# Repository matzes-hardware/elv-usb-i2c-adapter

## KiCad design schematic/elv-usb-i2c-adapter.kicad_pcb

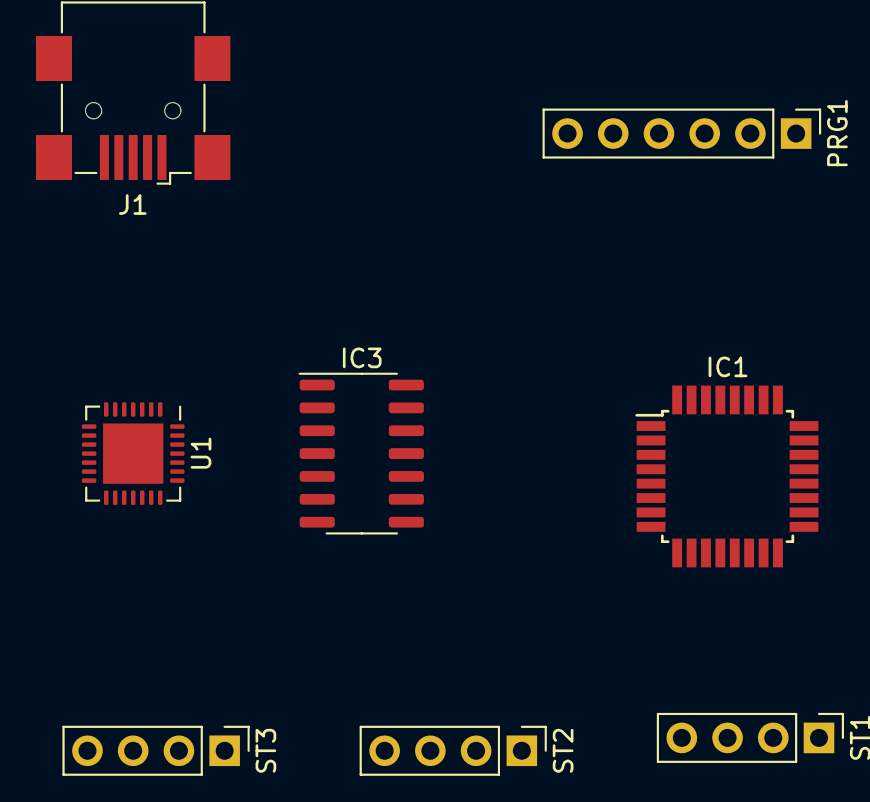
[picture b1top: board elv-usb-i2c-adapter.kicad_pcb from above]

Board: 2 copper layers, 8 parts (0 on the bottom side), 12 nets, no tracks yet.

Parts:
IC1: ATmega88PA-AU; TQFP-32_7x7mm_P0.8mm
IC3: 74HC14; SOIC-14_3.9x8.7mm_P1.27mm
J1: USB_B_Mini; USB_Mini-B_Wuerth_65100516121_Horizontal
PRG1: Conn_01x06; PinHeader_1x06_P2.54mm_Vertical
ST1, ST2, ST3: Conn_01x04; PinHeader_1x04_P2.54mm_Vertical
U1: CP2102; QFN-28-1EP_5x5mm_P0.5mm_EP3.35x3.35mm

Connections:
+5V: IC1.4, IC1.6, IC1.18, IC1.20, IC3.14, J1.1, PRG1.2, ST1.1, ST2.1, ST3.1
/DM: J1.2, U1.5
/DP: J1.3, U1.4
/MISO: IC1.16, PRG1.3
/MOSI: IC1.15, PRG1.4
/RESET: IC1.29, PRG1.5
/RX: IC1.30, IC3.6
/SCK: IC1.17, PRG1.1
/SCL: IC1.28, ST1.2, ST2.2, ST3.2
/SDA: IC1.27, ST1.3, ST2.3, ST3.3
/SUSPEND: IC1.32, U1.12
GND: IC1.3, IC1.5, IC1.21, IC3.1, IC3.3, IC3.7, IC3.11, IC3.13, J1.5, J1.6, PRG1.6, ST1.4, ST2.4, ST3.4, U1.3, U1.29

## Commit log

2021-08-12 Empty KiCad project
2021-08-12 Added components
2021-08-14 Renamed KiCad folder
2021-08-14 Creating a schematic
2021-08-14 Addec docs and downloads
2021-08-18 Renamed kicad/ -> schematic/
2021-08-18 Added CP2102
2025-02-27 Adding some fotos
